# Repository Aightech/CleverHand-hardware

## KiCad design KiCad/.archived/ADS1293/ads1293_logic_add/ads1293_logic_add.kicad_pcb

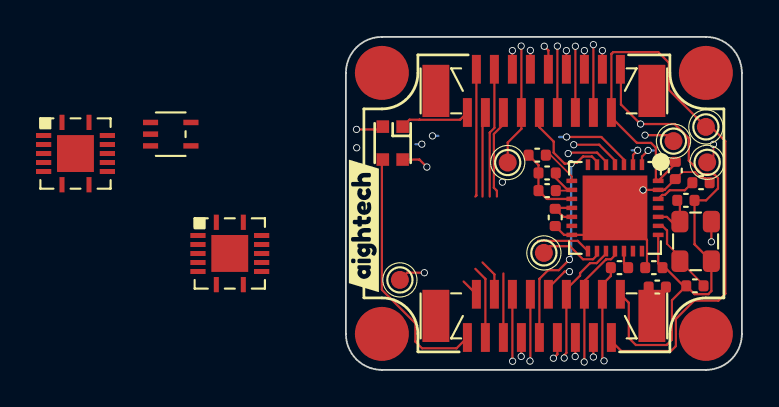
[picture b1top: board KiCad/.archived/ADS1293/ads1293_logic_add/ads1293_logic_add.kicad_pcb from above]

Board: 4 copper layers, 22.0 x 18.5 mm, 30 parts (0 on the bottom side), 33 nets.

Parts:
C1, C2: 22pF; C_0402_1005Metric
C3, C5, C7, C8: 100nF; C_0402_1005Metric
C4: 1uF; C_0402_1005Metric
C6: 1nF; C_0402_1005Metric
I1, I2, I3, I4: smd_insert; insert_1.2mm
J1, J2: XF2J-1824-12A
LED1: WS2812-2020
R1: 10K; C_0402_1005Metric
R2: 10M; C_0402_1005Metric
R3: 51; C_0402_1005Metric
TP5: TP_SCL; TestPoint_Pad_D1.0mm
TP6: TP_CS; TestPoint_Pad_D1.0mm
TP6#2: TP_AUX1; TestPoint_Pad_D1.0mm
TP8: TP_AUX3; TestPoint_Pad_D1.0mm
TP10: TP_SDA; TestPoint_Pad_D1.0mm
TP11: TP_AUX2; TestPoint_Pad_D1.0mm
U1: ADS1293CISQE-NOPB; ADS1293CISQE
U2: SN74LVC1G132DCKR
U3: SN74LVC86ARGYR
U4: SN74ALVC08RGYR
XTAL1: 4.096MHz; SMD3225-4P
kibuzzard-63F61033: G***; kibuzzard-63F61033

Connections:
+3.3V: C1.1, C2.1, C5.1, C8.1, J1.18, J2.1, LED1.4 (VDD), U1.22 (VDDIO), U2.5 (VCC), U3.5 (2B), U3.14 (VCC), U4.1 (1A), U4.14 (VCC), XTAL1.1 (EN)
+5VA: C3.1, J1.17, J2.2, TP11.1, U1.28 (VDD)
/ADS1293CISQE_0402_unit/CMOUT: R1.2, U1.8 (CMOUT)
/ADS1293CISQE_0402_unit/RLDINV: C6.1, R1.1, R2.1, U1.10 (RLDINV)
/ADS1293CISQE_0402_unit/RLDOUT: C6.2, R2.2, U1.9 (RLDOUT)
/ADS1293CISQE_0402_unit/RLDREF: C7.1, U1.11 (RLDIN), U1.12 (RLDREF)
/ADS1293CISQE_0402_unit/cvref: C4.1, U1.26 (CVREF)
/logic_address_unit/carry0: U3.2 (1B), U4.3 (1Y), U4.4 (2A)
/logic_address_unit/carry1: U3.13 (4B), U4.6 (2Y), U4.9 (3A)
/logic_address_unit/carry2: U2.1 (A), U3.10 (3B), U4.8 (3Y)
ADD_IN1: J1.2, U3.4 (2A), U4.2 (1B)
ADD_IN2: J1.3, U3.1 (1A), U4.5 (2B)
ADD_IN3: J1.4, U3.12 (4A), U4.10 (3B)
ADD_IN4: J1.5, U2.2 (B), U3.9 (3A)
ADD_OUT1: J2.17, U3.6 (2Y)
ADD_OUT2: J2.16, U3.3 (1Y)
ADD_OUT3: J2.15, U3.11 (4Y)
ADD_OUT4: J2.14, U3.8 (3Y)
AUX1: J1.11, J2.8, TP6#2.1
AUX2: J1.13, J2.6, TP8.1
AUX3: J1.8, J2.11
CSB: TP6.1, U1.16 (CSB), U2.4 (Y)
DIN: J1.14, J2.5, U1.18 (SDI)
DOUT: J1.16, J2.3, R3.2
GND: C3.2, C4.2, C5.2, C7.2, C8.2, J1.10, J1.15, J2.4, J2.9, LED1.2 (GND), TP10.1, U1.14 (VSSIO), U1.27 (VSS), U1.29 (EPAD), U2.3 (GND), U3.7 (GND), U3.15 (EPAD), U4.7 (GND), U4.15 (EPAD), XTAL1.2 (GND)
I2C_SCL: J1.7, J2.12, TP5.1
I2C_SDA: J1.6, J2.13
IN_ref: J1.9, J2.10, U1.6 (IN6)
LED_IN: J1.1, LED1.3 (DI)
LED_OUT: J2.18, LED1.1 (DO)
SCLK: J1.12, J2.7, U1.17 (SCLK)
XTAL1: C2.2, U1.23 (XTAL1), XTAL1.4 (i)
XTAL2: C1.2, U1.24 (XTAL2), XTAL1.3 (o)

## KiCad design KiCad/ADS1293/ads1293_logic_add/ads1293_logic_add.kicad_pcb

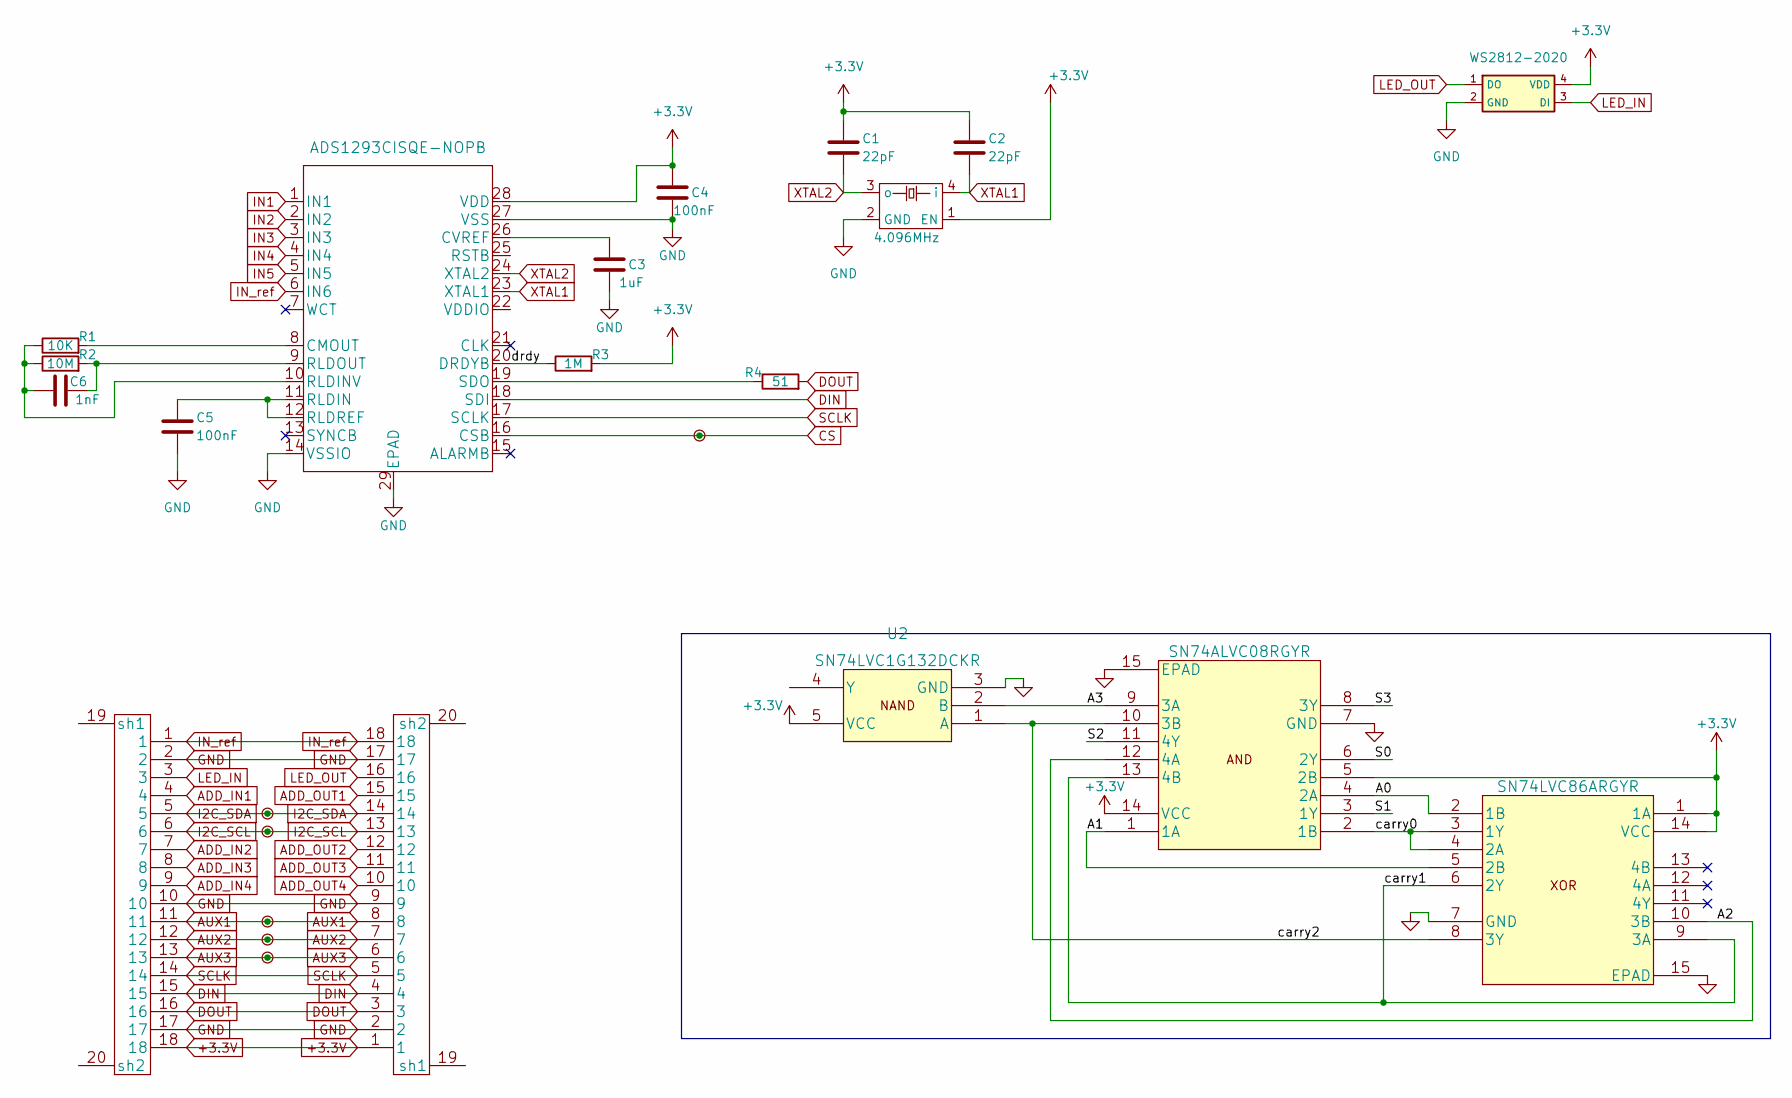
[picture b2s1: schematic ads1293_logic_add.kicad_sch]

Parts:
C1, C2: 22pF; C_0201_0603Metric
C3: 1uF; C_0201_0603Metric
C4, C5: 100nF; C_0201_0603Metric
C6: 1nF; C_0201_0603Metric
J1: COM_IN; XF2J-1824-12A
J2: COM_OUT; XF2J-1824-12A
LED1: WS2812-2020
R1: 10K; C_0201_0603Metric
R2: 10M; C_0201_0603Metric
R3: 1M; C_0201_0603Metric
R4: 51; C_0201_0603Metric
TP1: TP_SDA; TestPoint_Pad_D1.0mm
TP2: TP_SCL; TestPoint_Pad_D1.0mm
TP3: TP_AUX1; TestPoint_Pad_D1.0mm
TP4: TP_AUX2; TestPoint_Pad_D1.0mm
TP5: TP_AUX3; TestPoint_Pad_D1.0mm
TP6: TP_CS; TestPoint_Pad_D1.0mm
U1: ADS1293CISQE-NOPB; ADS1293CISQE
U2: SN74LVC1G132DCKR
U3: SN74ALVC08RGYR
U4: SN74LVC86ARGYR
XTAL1: 4.096MHz; SMD3225-4P

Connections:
+3.3V: C1.1, C2.1, C4.1, J1.18, J2.1, LED1.4 (VDD), R3.2, U1.28 (VDD), U2.5 (VCC), U3.5 (2B), U3.14 (VCC), U4.1 (1A), U4.14 (VCC), XTAL1.1 (EN)
/A0: U3.4 (2A), U4.2 (1B)
/A1: U3.1 (1A), U4.5 (2B)
/A2: U3.12 (4A), U4.10 (3B)
/A3: U2.2 (B), U3.9 (3A)
/S0: U3.6 (2Y)
/S1: U3.3 (1Y)
/S2: U3.11 (4Y)
/S3: U3.8 (3Y)
/carry0: U3.2 (1B), U4.3 (1Y), U4.4 (2A)
/carry1: U3.13 (4B), U4.6 (2Y), U4.9 (3A)
/carry2: U2.1 (A), U3.10 (3B), U4.8 (3Y)
/drdy: R3.1, U1.20 (DRDYB)
ADD_IN1: J1.4
ADD_IN2: J1.7
ADD_IN3: J1.8
ADD_IN4: J1.9
ADD_OUT1: J2.15
ADD_OUT2: J2.12
ADD_OUT3: J2.11
ADD_OUT4: J2.10
AUX1: J1.11, J2.8, TP3.1
AUX2: J1.12, J2.7, TP4.1
AUX3: J1.13, J2.6, TP5.1
CS: TP6.1, U1.16 (CSB)
DIN: J1.15, J2.4, U1.18 (SDI)
DOUT: J1.16, J2.3, R4.2
GND: C3.2, C4.2, C5.2, J1.2, J1.10, J1.17, J2.2, J2.9, J2.17, LED1.2 (GND), U1.14 (VSSIO), U1.27 (VSS), U1.29 (EPAD), U2.3 (GND), U3.7 (GND), U3.15 (EPAD), U4.7 (GND), U4.15 (EPAD), XTAL1.2 (GND)
I2C_SCL: J1.6, J2.13, TP2.1
I2C_SDA: J1.5, J2.14, TP1.1
IN1: U1.1 (IN1)
IN2: U1.2 (IN2)
IN3: U1.3 (IN3)
IN4: U1.4 (IN4)
IN5: U1.5 (IN5)
IN_ref: J1.1, J2.18, U1.6 (IN6)
LED_IN: J1.3, LED1.3 (DI)
LED_OUT: J2.16, LED1.1 (DO)
unnamed: C3.1, U1.26 (CVREF)
unnamed: C5.1, U1.11 (RLDIN), U1.12 (RLDREF)
unnamed: C6.1, R1.1, R2.1, U1.10 (RLDINV)
unnamed: C6.2, R2.2, U1.9 (RLDOUT)
unnamed: R1.2, U1.8 (CMOUT)
unnamed: R4.1, U1.19 (SDO)
SCLK: J1.14, J2.5, U1.17 (SCLK)
XTAL1: C2.2, U1.23 (XTAL1), XTAL1.4 (i)
XTAL2: C1.2, U1.24 (XTAL2), XTAL1.3 (o)

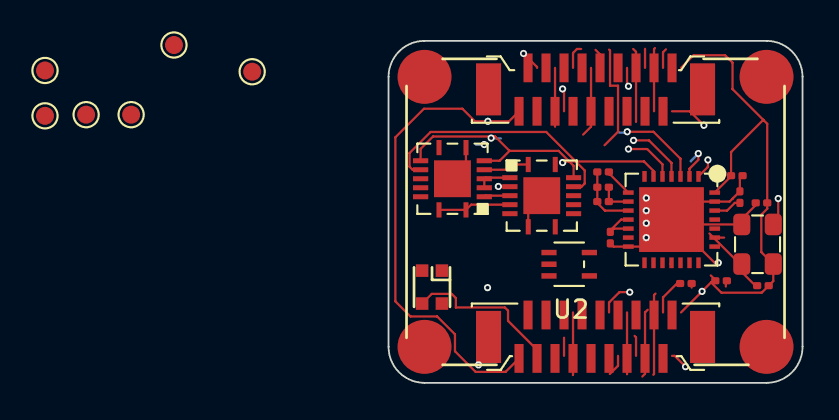
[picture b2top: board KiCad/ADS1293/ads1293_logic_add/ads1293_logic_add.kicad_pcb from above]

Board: 8 copper layers, 23.0 x 19.0 mm, 24 parts (0 on the bottom side), 30 nets.

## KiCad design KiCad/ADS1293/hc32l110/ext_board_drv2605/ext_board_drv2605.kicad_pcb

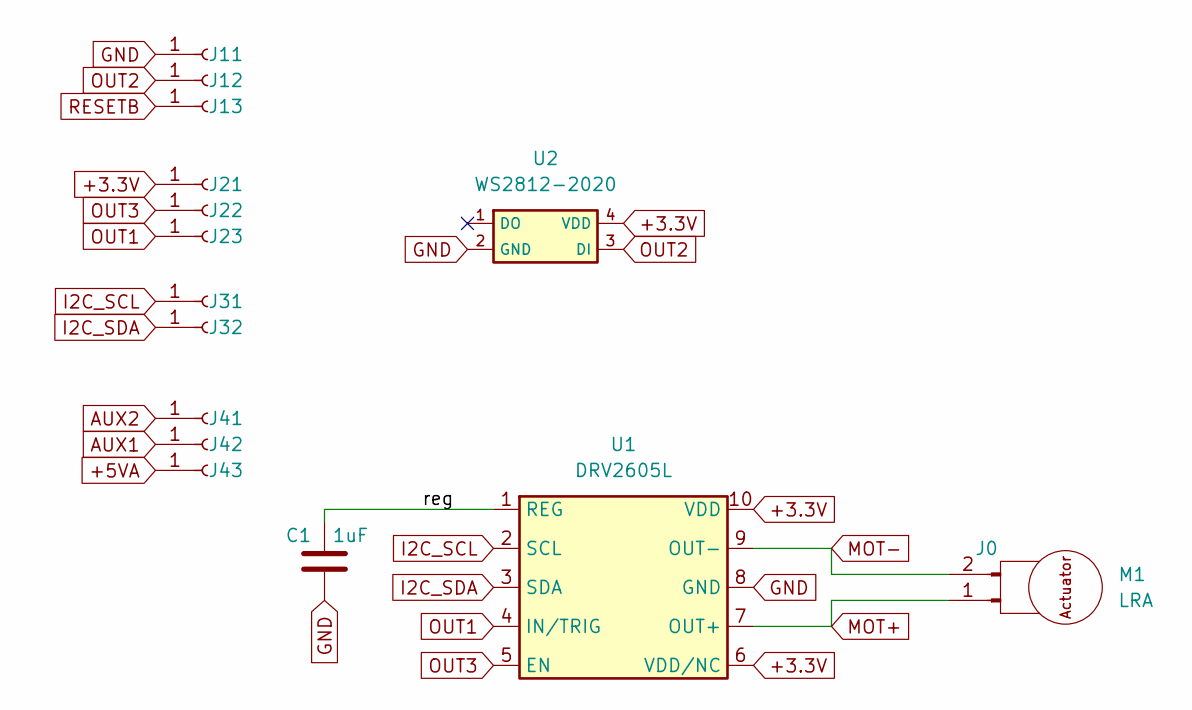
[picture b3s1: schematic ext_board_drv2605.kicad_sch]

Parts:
C1: 1uF; C_0201_0603Metric
J0: Conn_01x02_Male; PinHeader_1x02_P1.00mm_Vertical
J11, J12, J13, J21, J22, J23, J31, J32, J41, J42, J43: Conn_01x01_Female; Pin_D1.2mm_pogo
M1: LRA; LRA0832BE03L15
U1: DRV2605L; DRV2605L-VSSOP
U2: WS2812-2020

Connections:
+3.3V: J21.1, U1.6 (VDD/NC), U1.10 (VDD), U2.4 (VDD)
+5VA: J43.1
/reg: C1.1, U1.1 (REG)
AUX1: J42.1
AUX2: J41.1
GND: C1.2, J11.1, U1.8 (GND), U2.2 (GND)
I2C_SCL: J31.1, U1.2 (SCL)
I2C_SDA: J32.1, U1.3 (SDA)
MOT+: J0.1, U1.7 (OUT+)
MOT-: J0.2, U1.9 (OUT-)
OUT1: J23.1, U1.4 (IN/TRIG)
OUT2: J12.1, U2.3 (DI)
OUT3: J22.1, U1.5 (EN)
RESETB: J13.1

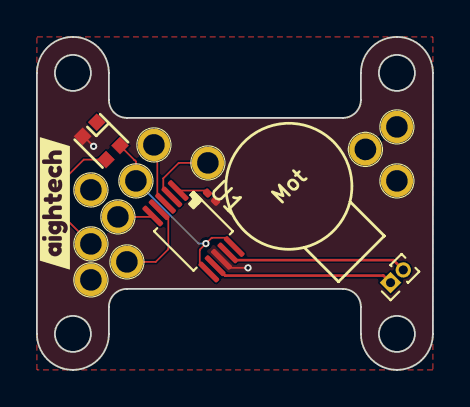
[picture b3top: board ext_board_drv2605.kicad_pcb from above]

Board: 2 copper layers, 22.0 x 18.5 mm, 17 parts (0 on the bottom side), 10 nets.

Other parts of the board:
kibuzzard-63F61033: G***; kibuzzard-63F61033

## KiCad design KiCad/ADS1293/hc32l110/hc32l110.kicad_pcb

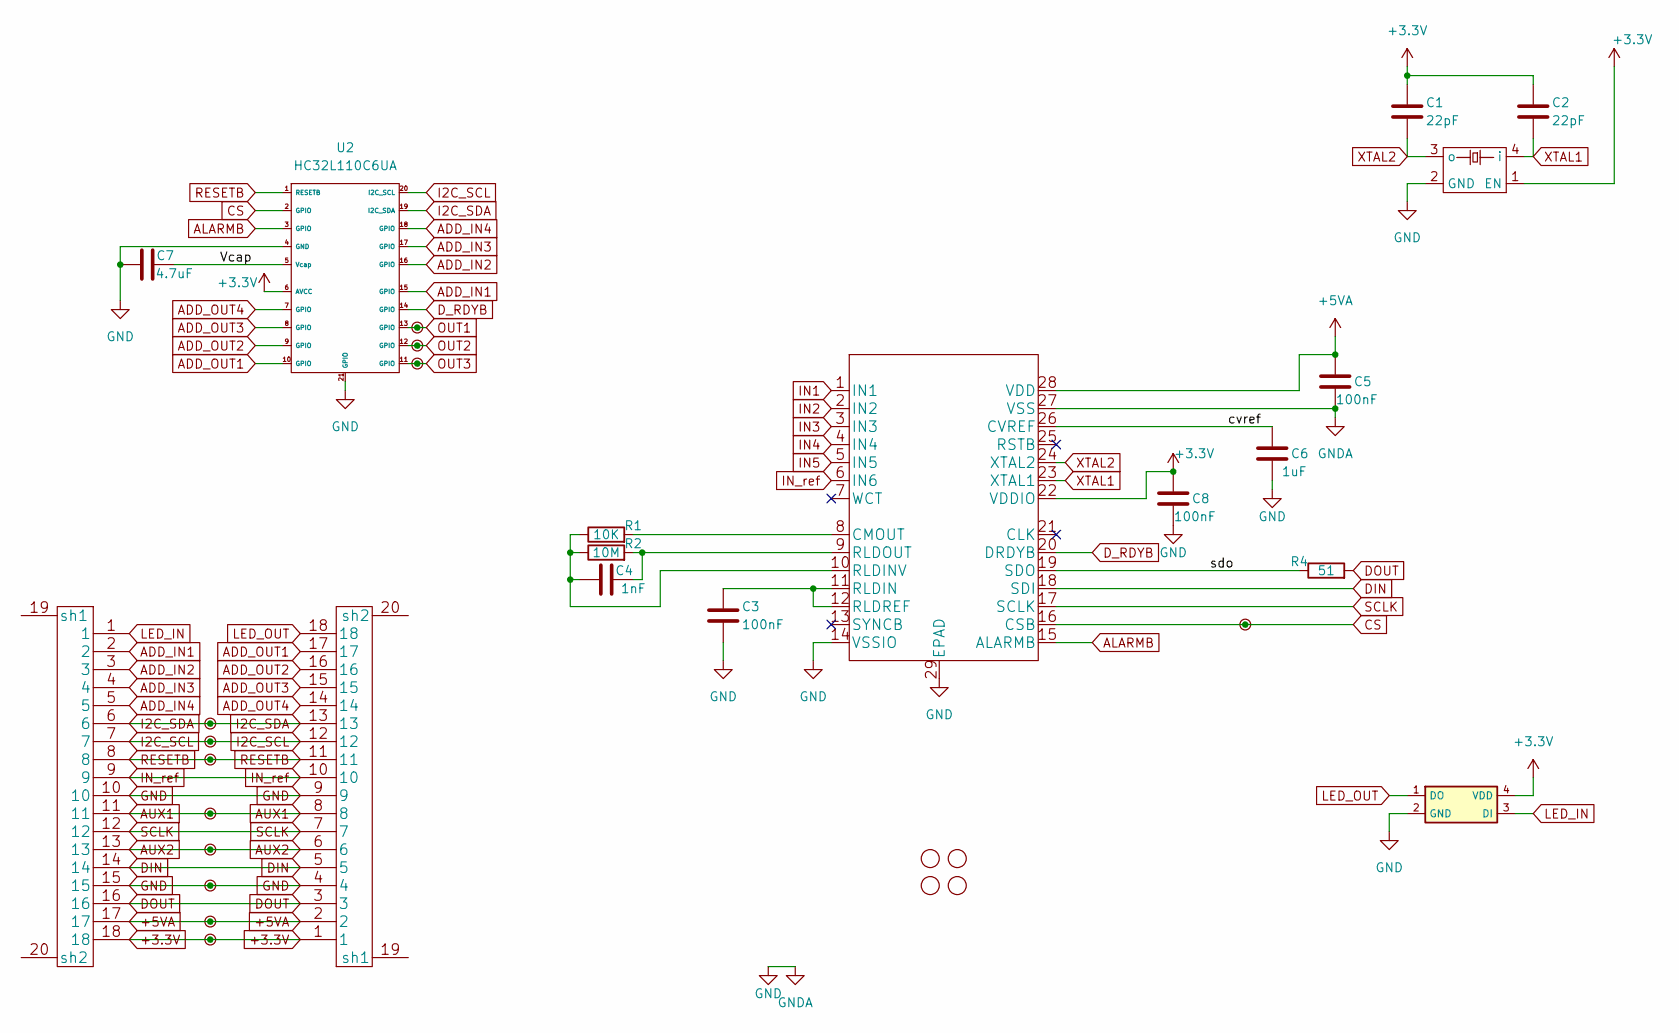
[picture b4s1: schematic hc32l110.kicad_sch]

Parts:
C1, C2: 22pF; C_0201_0603Metric
C3, C5, C8: 100nF; C_0201_0603Metric
C4: 1nF; C_0201_0603Metric
C6: 1uF; C_0201_0603Metric
C7: 4.7uF; C_0201_0603Metric
I1, I2, I3, I4: smd_insert; insert_1.2mm
J1: COM_IN; XF2J-1824-12A
J2: COM_OUT; XF2J-1824-12A
LED1: WS2812-2020
R1: 10K; C_0201_0603Metric
R2: 10M; C_0201_0603Metric
R4: 51; C_0201_0603Metric
TP1: TP_CS; TestPoint_Pad_D1.0mm
TP2, TP3, TP4, TP9, TP10: TP_SDA; TestPoint_Pad_D1.0mm
TP5: TP_SCL; TestPoint_Pad_D1.0mm
TP6: TP_AUX1; TestPoint_Pad_D1.0mm
TP7, TP11, TP12: TP_AUX2; TestPoint_Pad_D1.0mm
TP8: TP_AUX3; TestPoint_Pad_D1.0mm
U1: ADS1293CISQE-NOPB; ADS1293CISQE
U2: HC32L110C6UA; QFN-20-1EP_3x3mm_P0.4mm_EP1.4x1.4mm
XTAL1: 4.096MHz; SMD3225-4P

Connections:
+3.3V: C1.1, C2.1, C8.1, J1.18, J2.1, LED1.4 (VDD), TP12.1, U1.22 (VDDIO), U2.6 (AVCC), XTAL1.1 (EN)
+5VA: C5.1, J1.17, J2.2, TP11.1, U1.28 (VDD)
/Vcap: C7.2, U2.5 (Vcap)
/cvref: C6.1, U1.26 (CVREF)
/sdo: R4.1, U1.19 (SDO)
ADD_IN1: J1.2, U2.15 (GPIO)
ADD_IN2: J1.3, U2.16 (GPIO)
ADD_IN3: J1.4, U2.17 (GPIO)
ADD_IN4: J1.5, U2.18 (GPIO)
ADD_OUT1: J2.17, U2.10 (GPIO)
ADD_OUT2: J2.16, U2.9 (GPIO)
ADD_OUT3: J2.15, U2.8 (GPIO)
ADD_OUT4: J2.14, U2.7 (GPIO)
ALARMB: U1.15 (ALARMB), U2.3 (GPIO)
AUX1: J1.11, J2.8, TP6.1
AUX2: J1.13, J2.6, TP8.1
CS: TP1.1, U1.16 (CSB), U2.2 (GPIO)
DIN: J1.14, J2.5, U1.18 (SDI)
DOUT: J1.16, J2.3, R4.2
D_RDYB: U1.20 (DRDYB), U2.14 (GPIO)
GND: C3.2, C5.2, C6.2, C7.1, C8.2, J1.10, J1.15, J2.4, J2.9, LED1.2 (GND), TP10.1, U1.14 (VSSIO), U1.27 (VSS), U1.29 (EPAD), U2.4 (GND), U2.21 (GPIO), XTAL1.2 (GND)
I2C_SCL: J1.7, J2.12, TP5.1, U2.20 (I2C_SCL)
I2C_SDA: J1.6, J2.13, TP4.1, U2.19 (I2C_SDA)
IN1: U1.1 (IN1)
IN2: U1.2 (IN2)
IN3: U1.3 (IN3)
IN4: U1.4 (IN4)
IN5: U1.5 (IN5)
IN_ref: J1.9, J2.10, U1.6 (IN6)
LED_IN: J1.1, LED1.3 (DI)
LED_OUT: J2.18, LED1.1 (DO)
unnamed: R1.2, U1.8 (CMOUT)
unnamed: C3.1, U1.11 (RLDIN), U1.12 (RLDREF)
unnamed: C4.1, R1.1, R2.1, U1.10 (RLDINV)
unnamed: C4.2, R2.2, U1.9 (RLDOUT)
OUT1: TP2.1, U2.13 (GPIO)
OUT2: TP3.1, U2.12 (GPIO)
OUT3: TP9.1, U2.11 (GPIO)
RESETB: J1.8, J2.11, TP7.1, U2.1 (RESETB)
SCLK: J1.12, J2.7, U1.17 (SCLK)
XTAL1: C2.2, U1.23 (XTAL1), XTAL1.4 (i)
XTAL2: C1.2, U1.24 (XTAL2), XTAL1.3 (o)

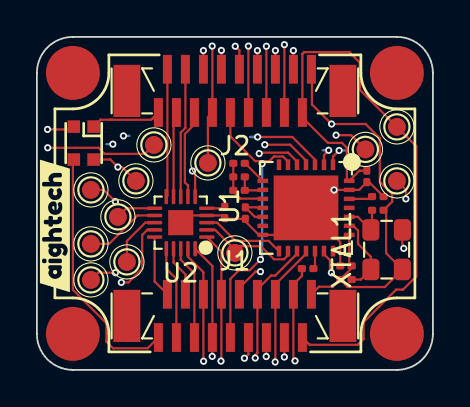
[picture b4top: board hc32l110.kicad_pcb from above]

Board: 4 copper layers, 22.0 x 18.5 mm, 34 parts (0 on the bottom side), 37 nets.

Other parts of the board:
kibuzzard-63F61033: G***; kibuzzard-63F61033

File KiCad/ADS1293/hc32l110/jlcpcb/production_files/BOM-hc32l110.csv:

Comment,Designator,Footprint,LCSC
10K,R1,C_0201_0603Metric,C106225
ADS1293CISQE-NOPB,U1,ADS1293CISQE,C181260
4.096MHz,XTAL1,SMD3225-4P,C255991
22pF,"C1,C2",C_0201_0603Metric,C272881
10M,R2,C_0201_0603Metric,C320452
51,R4,C_0201_0603Metric,C320945
4.7uF,C7,C_0201_0603Metric,C335103
XF2J-1824-12A,"J1,J2",XF2J-1824-12A,C397324
HC32L110C6UA,U2,QFN-20-1EP_3x3mm_P0.4mm_EP1.4x1.4mm,C493490
1nF,C4,C_0201_0603Metric,C526941
1uF,C6,C_0201_0603Metric,C53067
100nF,"C3,C5,C8",C_0201_0603Metric,C66938
WS2812-2020,LED1,WS2812-2020,C965555

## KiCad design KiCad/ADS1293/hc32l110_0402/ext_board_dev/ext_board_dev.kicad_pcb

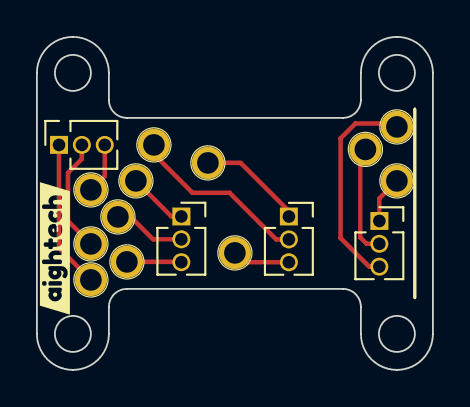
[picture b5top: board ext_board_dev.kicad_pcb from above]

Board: 4 copper layers, 22.0 x 18.5 mm, 17 parts (0 on the bottom side), 12 nets.

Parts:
J1, J2, J3, J4: Conn_01x03_Male; PinSocket_1x03_P1.27mm_Vertical
J11, J12, J13, J21, J22, J23, J31, J32, J33, J41, J42, J43: Conn_01x01_Female; Pin_D1.2mm_pogo
kibuzzard-63F61033: G***; kibuzzard-63F61033

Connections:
+3.3V: J2.1, J21.1
+5VA: J4.3, J43.1
AUX1: J4.2, J42.1
AUX2: J4.1, J41.1
CS: J3.3, J33.1
I2C_SCL: J3.1, J31.1
I2C_SDA: J3.2, J32.1
unnamed: J1.1, J11.1
unnamed: J1.2, J12.1
unnamed: J1.3, J13.1
OUT1: J2.3, J23.1
OUT3: J2.2, J22.1
